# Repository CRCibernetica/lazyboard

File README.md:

# LazyBoard
 A minimal esp32-s3 dev board for ULP prototyping and experimentation
 
 Q: Why is the board lazy? A: Because it's always sleeping!

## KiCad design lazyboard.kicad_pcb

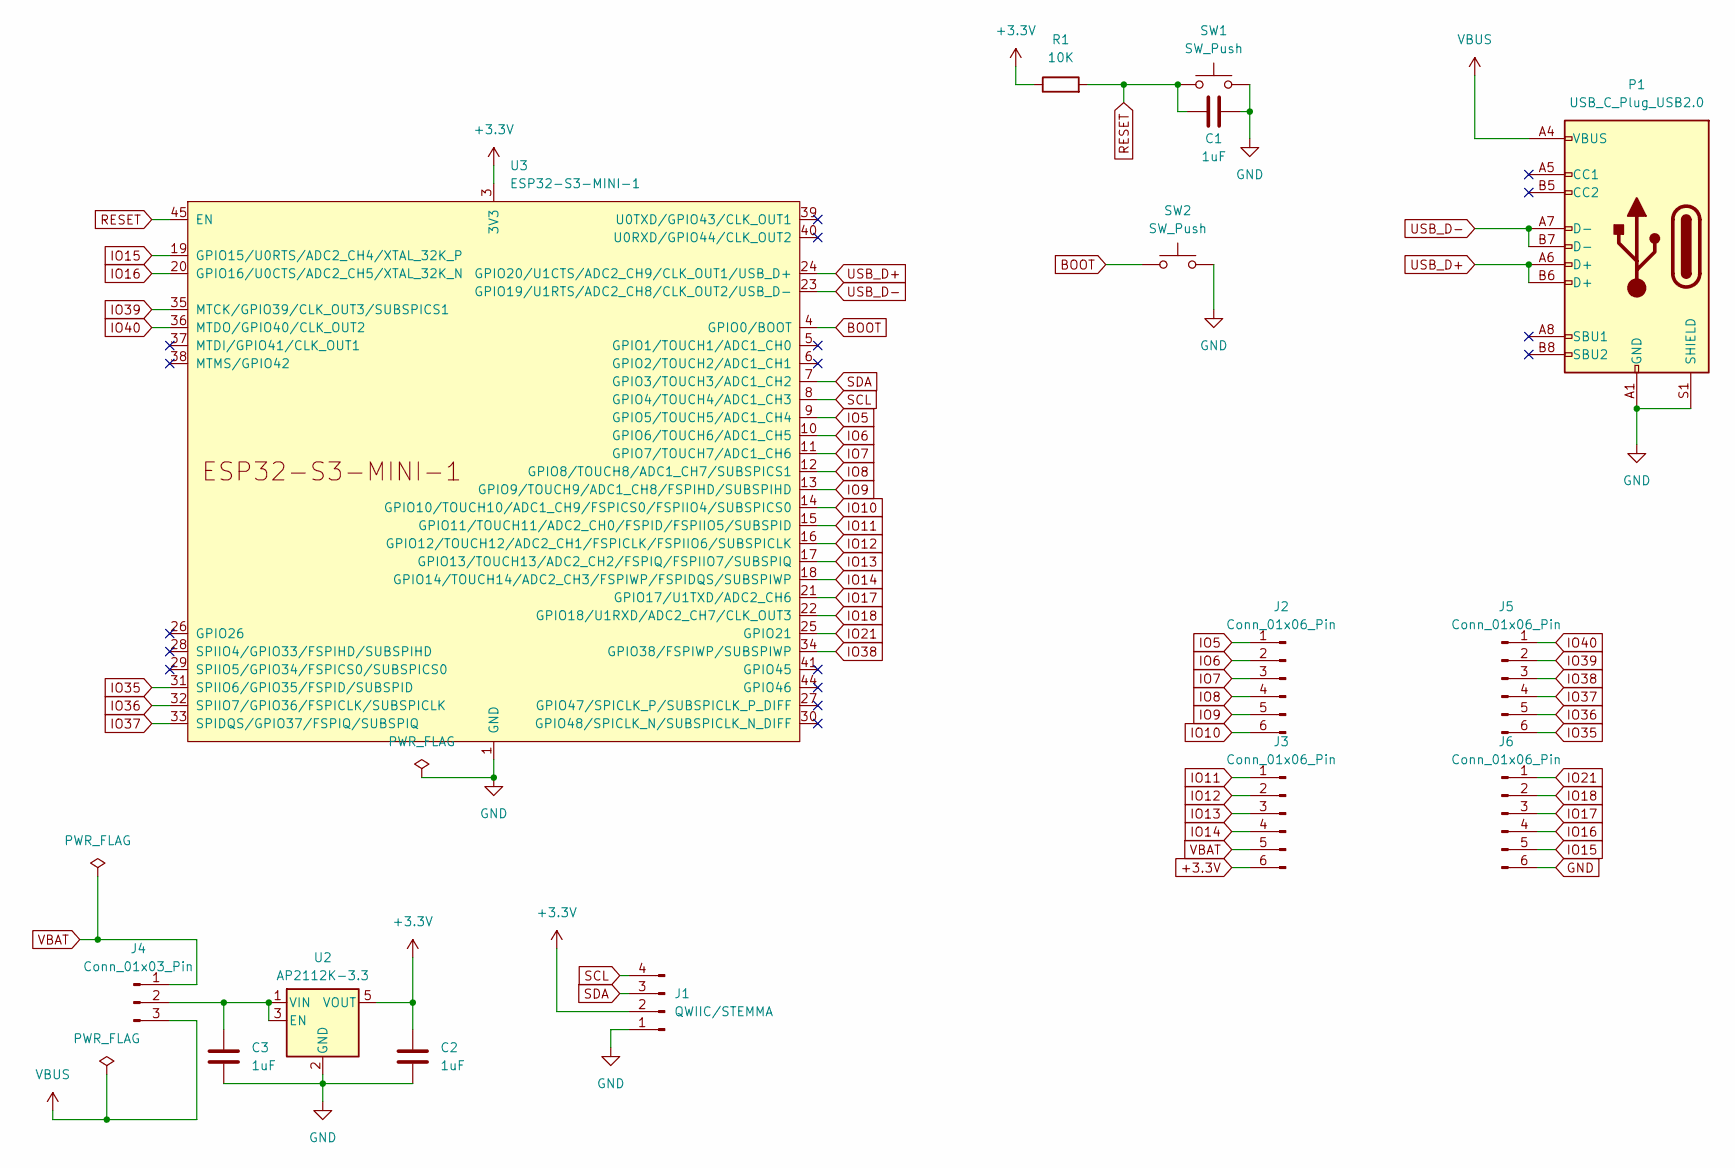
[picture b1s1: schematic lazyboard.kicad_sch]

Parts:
C1, C2, C3: 1uF; C_0603_1608Metric
J1: QWIIC/STEMMA; JST_SH_SM04B-SRSS-TB_1x04-1MP_P1.00mm_Horizontal
J2, J3, J5, J6: Conn_01x06_Pin; PinHeader_1x06_P2.54mm_Vertical
J4: Conn_01x03_Pin; PinHeader_1x03_P2.54mm_Vertical
P1: USB_C_Plug_USB2.0; USB_C_Receptacle_GCT_USB4105-xx-A_16P_TopMnt_Horizontal
R1: 10K; R_0603_1608Metric
SW1, SW2: SW_Push; SW_Push_SPST_NO_Alps_SKRK
U2: AP2112K-3.3; SOT-23-5
U3: ESP32-S3-MINI-1

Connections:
+3.3V: C2.1, J1.2, J3.6, R1.1, U2.5 (VOUT), U3.3 (3V3)
BOOT: SW2.2, U3.4 (GPIO0/BOOT)
GND: C1.2, C2.2, C3.2, J1.1, J6.6, P1.A1 (GND), P1.A12 (GND), P1.B1 (GND), P1.B12 (GND), P1.S1 (SHIELD), SW1.2, SW2.1, U2.2 (GND), U3.1 (GND), U3.2 (GND), U3.42 (GND), U3.43 (GND), U3.46 (GND), U3.47 (GND), U3.48 (GND), U3.49 (GND), U3.50 (GND), U3.51 (GND), U3.52 (GND), U3.53 (GND), U3.54 (GND), U3.55 (GND), U3.56 (GND), U3.57 (GND), U3.58 (GND), U3.59 (GND), U3.60 (GND), U3.61 (GND), U3.62 (GND), U3.63 (GND), U3.64 (GND), U3.65 (GND)
IO5: J2.1, U3.9 (GPIO5/TOUCH5/ADC1_CH4)
IO6: J2.2, U3.10 (GPIO6/TOUCH6/ADC1_CH5)
IO7: J2.3, U3.11 (GPIO7/TOUCH7/ADC1_CH6)
IO8: J2.4, U3.12 (GPIO8/TOUCH8/ADC1_CH7/SUBSPICS1)
IO9: J2.5, U3.13 (GPIO9/TOUCH9/ADC1_CH8/FSPIHD/SUBSPIHD)
IO10: J2.6, U3.14 (GPIO10/TOUCH10/ADC1_CH9/FSPICS0/FSPIIO4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)
IO11: J3.1, U3.15 (GPIO11/TOUCH11/ADC2_CH0/FSPID/FSPIIO5/S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)
IO12: J3.2, U3.16 (GPIO12/TOUCH12/ADC2_CH1/FSPICLK/FSPIIO6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)
IO13: J3.3, U3.17 (GPIO13/TOUCH13/ADC2_CH2/FSPIQ/FSPIIO7/S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)
IO14: J3.4, U3.18 (GPIO14/TOUCH14/ADC2_CH3/FSPIWP/FSPIDQS/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)
IO15: J6.5, U3.19 (GPIO15/U0RTS/ADC2_CH4/XTAL_32K_P)
IO16: J6.4, U3.20 (GPIO16/U0CTS/ADC2_CH5/XTAL_32K_N)
IO17: J6.3, U3.21 (GPIO17/U1TXD/ADC2_CH6)
IO18: J6.2, U3.22 (GPIO18/U1RXD/ADC2_CH7/CLK_OUT3)
IO21: J6.1, U3.25 (GPIO21)
IO35: J5.6, U3.31 (SPIIO6/GPIO35/FSPID/SUBSPID)
IO36: J5.5, U3.32 (SPIIO7/GPIO36/FSPICLK/SUBSPICLK)
IO37: J5.4, U3.33 (SPIDQS/GPIO37/FSPIQ/SUBSPIQ)
IO38: J5.3, U3.34 (GPIO38/FSPIWP/SUBSPIWP)
IO39: J5.2, U3.35 (MTCK/GPIO39/CLK_OUT3/SUBSPICS1)
IO40: J5.1, U3.36 (MTDO/GPIO40/CLK_OUT2)
unnamed: C3.1, J4.2, U2.1 (VIN), U2.3 (EN)
RESET: C1.1, R1.2, SW1.1, U3.45 (EN)
SCL: J1.4, U3.8 (GPIO4/TOUCH4/ADC1_CH3)
SDA: J1.3, U3.7 (GPIO3/TOUCH3/ADC1_CH2)
USB_D+: P1.A6 (D+), P1.B6 (D+), U3.24 (GPIO20/U1CTS/ADC2_CH9/CLK_OUT1/USB_D+)
USB_D-: P1.A7 (D-), P1.B7 (D-), U3.23 (GPIO19/U1RTS/ADC2_CH8/CLK_OUT2/USB_D-)
VBAT: J3.5, J4.1
VBUS: J4.3, P1.A4 (VBUS), P1.A9 (VBUS), P1.B4 (VBUS), P1.B9 (VBUS)

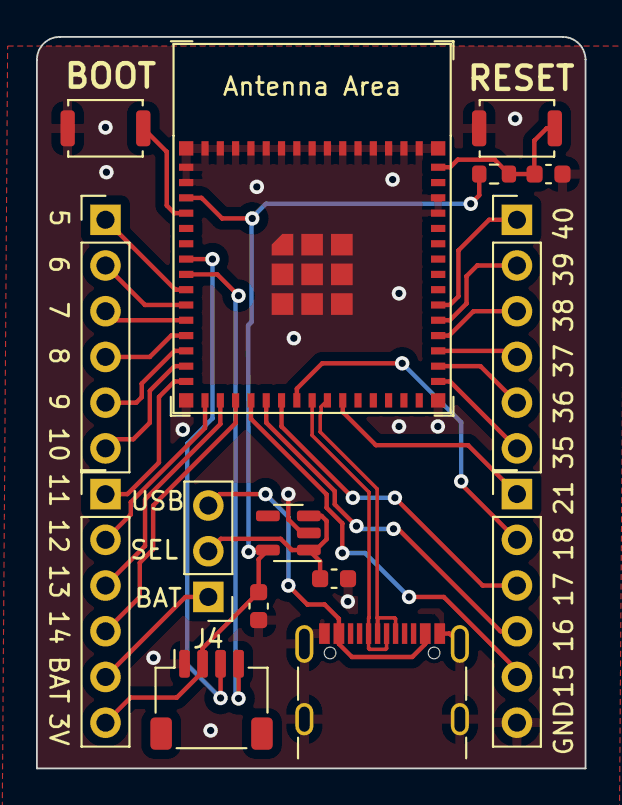
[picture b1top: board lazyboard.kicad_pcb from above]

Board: 2 copper layers, 30.5 x 40.6 mm, 15 parts (0 on the bottom side), 32 nets.

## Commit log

2023-11-23 fixed reset bug
